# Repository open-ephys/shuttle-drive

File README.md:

# Shuttle-drive, the next gen. tetrode drive implant 

Tetrode arrays are the gold-standard method for neural recordings in many studies with behaving animals, especially for deep structures and chronic recordings. Here we outline an improved drive design for use in freely behaving animals. Our design makes use of recently developed technologies to reduce the complexity and build time of the drive while maintaining a low weight. The design also presents an improvement over many existing designs in terms of robustness and ease of use. We describe two variants: a 16 tetrode implant weighing ∼2 g for mice, bats, tree shrews and similar animals, and a 64 tetrode implant weighing ∼16 g for rats, and similar animals.These designs were co-developed and optimized alongside a new class of drive-mounted feature-rich amplifier boards with ultra-thin RF tethers, as described in an upcoming paper (Newman, Zhang et al., in prep). This design significantly improves the data yield of chronic electrophysiology experiments.

### Features

__64-Channel Drive__
- Channel count (small version): 18 drive mechanisms and up to 64 ephys channels per drive.
- Weight: ~2g for 16 tetrode drives.
- Build time:  < 1 day (small version).
- 4.5 mm travel distance, fully enclosed mechanism, low center of gravity. 

__256-Channel Drive__
- Channel count: 64 drive mechanisms and up to 256 ephys channels per drive.
- Weight: ~15g for 64 tetrode drives.
- 10 mm travel distance, fully enclosed mechanism, low center of gravity)

### Components & Availability

Ready-made drive components are available for purchase at the Open Ephy store
[here](http://www.open-ephys.org/drive-implant). All profits go towards
supporting the Open Ephys initiative if, and only if, parts are bought via this
store.

The drive consists of the following components:
- A 3d printed drive body
- 3d printed drive shuttles
- Polymicro (polyimide-coated quartz) shuttle tubes

These components can be purchased as bundle on our store:
- Polyimide tubes to make guide tube arrays 
- Custom screws (reusable) 
- Electrode interface boards (EIB) are available for 64 channel or 32 channel Omnetics headstages 

To assemble the drive and adjust tetrodes, an assembly jig and screwdriver are
needed. Both are available on the Open Ephys store.
- Assembly jig 
- Custom screwdriver 

### Building instructions & Documentation

For a quick initial overview, we provide a brief video detailing all the major steps of assembling the drive: [Assembly steps on youtube](https://www.youtube.com/watch?v=VBs4_pltE6o&feature=emb_logo).

The main documentation and building instructions are in the accompanying manuscript:

[Voigts et al.  An
easy-to-assemble, robust, and lightweight drive implant for chronic tetrode
recordings in freely moving animals](https://www.biorxiv.org/content/10.1101/746651v1). We recommend this manuscript as a starting point because it covers a lot of possible issues and goes into considerable detail on how to achieve the best results.

**A structured, up to date documentation is on the Open Ephys docs**: [https://open-ephys.github.io/shuttledrive-docs/](https://open-ephys.github.io/shuttledrive-docs/)

We also provide a [spreadsheet with step-by-step instructions](https://docs.google.com/spreadsheets/d/1qlOEyMCUptONbd9Ac4yKie1TxPHhV1puGx7GZTR9lvk/edit?usp=sharing), provided by Dimitra Vardalaki.

Finally, we encourage contributions from anyone, particularly additional information on variants and build instructions in nay form, including pull-requests or links to external documentation.

### Parts List / Bill of Materials
The bill of materials is located on this [google sheet](https://docs.google.com/spreadsheets/d/1LGhZMRnzcyo_r0Nunrh_lfmy5V0NHia-rGRHAYOWq4o/edit?usp=sharing)

### Citing this Work 
When using the Open Ephys shuttle drive implants, please cite the paper:

An easy-to-assemble, robust, and lightweight drive implant for chronic tetrode recordings in freely moving animals
J Voigts, JP Newman, MA Wilson, MT Harnett
Journal of Neural Engineering 17 (2), 026044
 [Link jne](https://iopscience.iop.org/article/10.1088/1741-2552/ab77f9/meta) [Link biorxiv](https://www.biorxiv.org/content/10.1101/746651v1) 

## License
Copyright Jakob Voigts, Jonathan P. Newman 2020.

<br />This work is licensed under a <a rel="license" href="http://creativecommons.org/licenses/by-nc-sa/3.0/igo/">Creative Commons Attribution-NonCommercial-ShareAlike 3.0 IGO License</a>.

If your are interested in obtaining a license to sell this device, please contact us at https://open-ephys.org/contact

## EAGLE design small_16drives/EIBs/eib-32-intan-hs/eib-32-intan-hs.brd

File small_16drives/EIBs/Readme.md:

# Omnetics EIBs for Open Ephys Shuttledrive

**(Deprecated)** We do not recommend using these EIBs any longer, instead consider switching to the hirose based EIBs (https://open-ephys.org/drive-implant/64-channel-eib-lyfw2) together with the newer low-profile headstage https://open-ephys.org/acquisition-system/low-profile-spi-headstage-64ch. In the longer term, consider using the upcoming ONIX system with this drive.

For the 64 channel variant, extra care is required to keep a precise alignment between the two omnetics connectors.

The EIB for the ONIX system and the SPI compatible low profile hedstage are found in the ONIX system repository at https://github.com/jonnew/ONIX/tree/main/eib-64

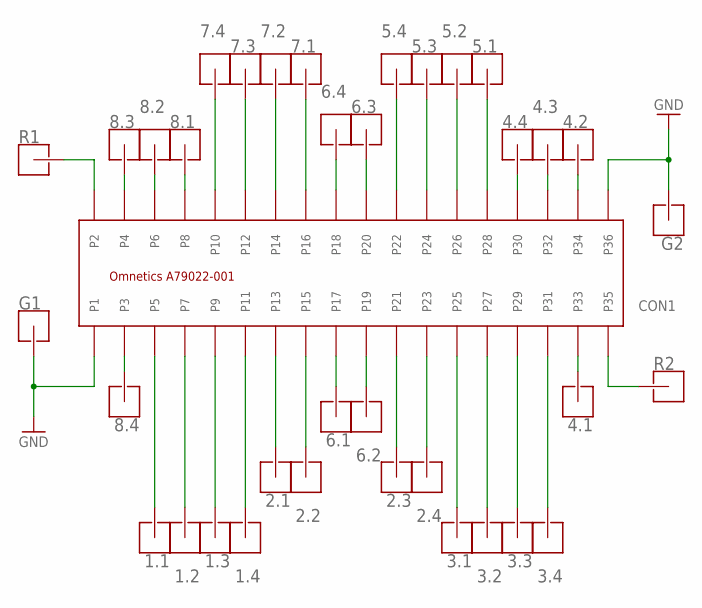
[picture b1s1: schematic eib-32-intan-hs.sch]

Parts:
1.1, 1.2, 1.3, 1.4, 2.1, 2.2, 2.3, 2.4, 3.1, 3.2, 3.3, 3.4, 4.1, 4.2, 4.3, 4.4, 5.1, 5.2, 5.3, 5.4, 6.1, 6.2, 6.3, 6.4, 7.1, 7.2, 7.3, 7.4, 8.1, 8.2, 8.3, 8.4: HOLE_L_G_PIN_V7; LARGE_GOLD_PIN_V7
CON1: A79022-001_MALESMD; A79026-001_MALE
G1, G2: HOLE_L_G_PIN_V7; LARGE_GOLD_PIN_V7
R1, R2: HOLE_L_G_PIN_V7; LARGE_GOLD_PIN_V7

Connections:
GND: CON1.P1, CON1.P36, G1.P$1, G2.P$1
unnamed: 1.1.P$1, CON1.P5
unnamed: 1.2.P$1, CON1.P7
unnamed: 1.3.P$1, CON1.P9
unnamed: 4.1.P$1, CON1.P33
unnamed: 4.3.P$1, CON1.P32
unnamed: 4.2.P$1, CON1.P34
unnamed: 1.4.P$1, CON1.P11
unnamed: 4.4.P$1, CON1.P30
unnamed: 6.1.P$1, CON1.P17
unnamed: 6.2.P$1, CON1.P19
unnamed: 6.3.P$1, CON1.P20
unnamed: 7.3.P$1, CON1.P12
unnamed: 2.1.P$1, CON1.P13
unnamed: 2.2.P$1, CON1.P15
unnamed: 2.3.P$1, CON1.P21
unnamed: 2.4.P$1, CON1.P23
unnamed: 3.1.P$1, CON1.P25
unnamed: 3.2.P$1, CON1.P27
unnamed: 3.3.P$1, CON1.P29
unnamed: 3.4.P$1, CON1.P31
unnamed: 6.4.P$1, CON1.P18
unnamed: 8.4.P$1, CON1.P3
unnamed: 8.3.P$1, CON1.P4
unnamed: 8.2.P$1, CON1.P6
unnamed: 8.1.P$1, CON1.P8
unnamed: 7.2.P$1, CON1.P14
unnamed: 7.1.P$1, CON1.P16
unnamed: 7.4.P$1, CON1.P10
unnamed: 5.1.P$1, CON1.P28
unnamed: 5.2.P$1, CON1.P26
unnamed: 5.4.P$1, CON1.P22
unnamed: 5.3.P$1, CON1.P24
unnamed: CON1.P2, R1.P$1
unnamed: CON1.P35, R2.P$1

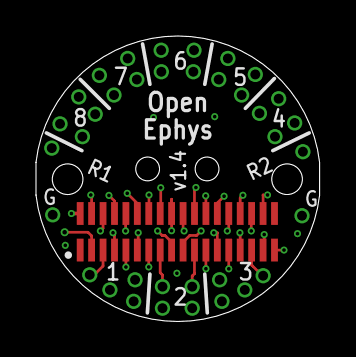
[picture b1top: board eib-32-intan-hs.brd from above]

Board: 4 copper layers, 15.8 x 15.9 mm, 37 parts (0 on the bottom side), 35 nets.

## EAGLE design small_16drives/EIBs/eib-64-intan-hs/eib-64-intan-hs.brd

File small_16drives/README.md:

# shuttleDrive-16

Mouse version of the next generation tetrode drive implant.

This is the variant for 16 drives.
The bill of materials can be found at https://docs.google.com/spreadsheets/d/1LGhZMRnzcyo_r0Nunrh_lfmy5V0NHia-rGRHAYOWq4o/edit?usp=sharing

Additional assembly instructions can be found at https://docs.google.com/spreadsheets/d/1qlOEyMCUptONbd9Ac4yKie1TxPHhV1puGx7GZTR9lvk/edit?usp=sharing

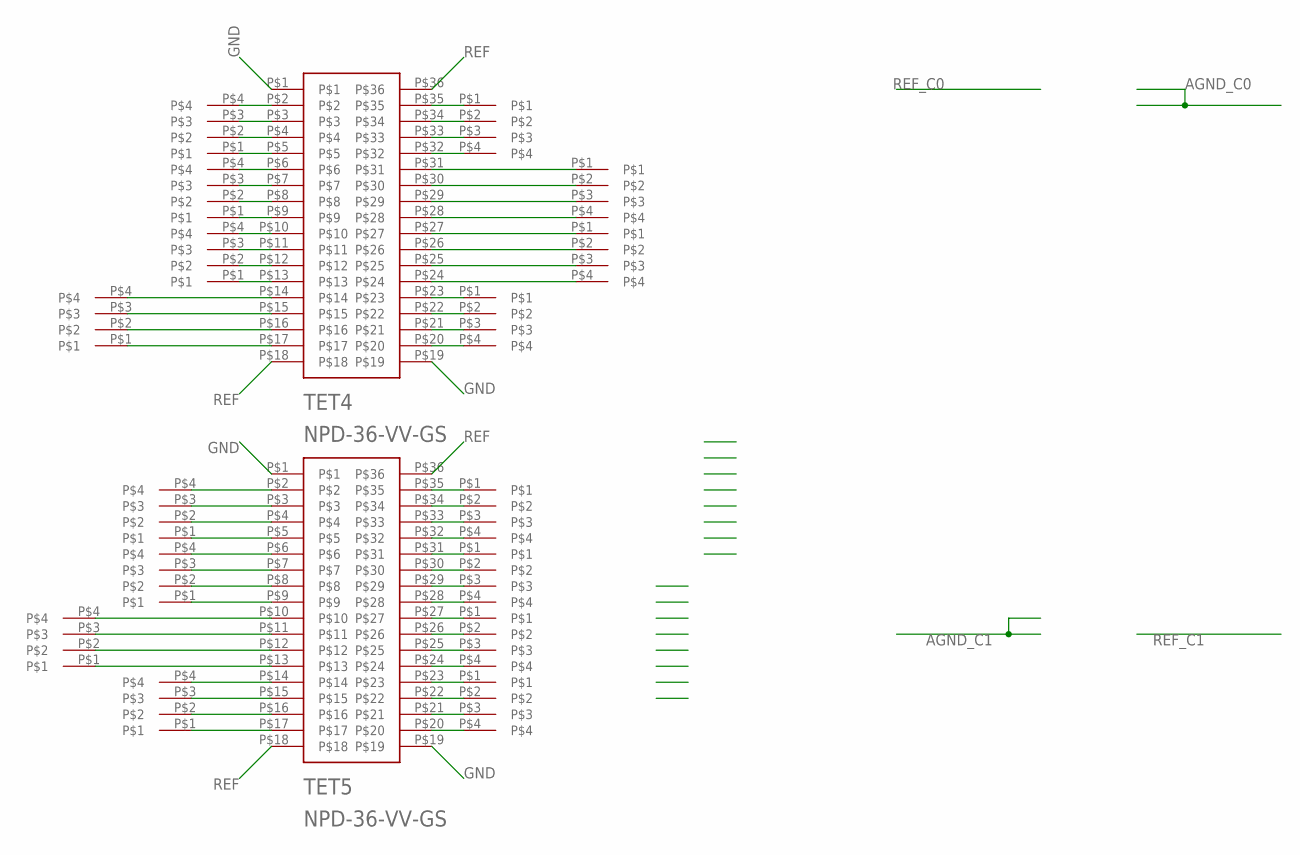
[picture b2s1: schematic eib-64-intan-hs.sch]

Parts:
TET0: 0; TET32
TET1: 1; TET32
TET2: 2; TET32
TET3: 3; TET32
TET4, TET5: NPD-36-VV-GS
TET8: 8; TET32
TET9: 9; TET32
TET10: 10; TET32
TET11: 11; TET32
TET12: 12; TET32
TET13: 13; TET32
TET14: 14; TET32
TET15: 15; TET32
TET20: 20; TET32
TET21: 21; TET32
TET22: 22; TET32
TET23: 23; TET32

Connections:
GND: TET4.P$1, TET4.P$19, TET5.P$1, TET5.P$19
unnamed: TET5.P$6, TET9.P$4
unnamed: TET5.P$2, TET8.P$4
unnamed: TET5.P$3, TET8.P$3
unnamed: TET5.P$4, TET8.P$2
unnamed: TET5.P$5, TET8.P$1
unnamed: TET5.P$7, TET9.P$3
unnamed: TET5.P$8, TET9.P$2
unnamed: TET5.P$9, TET9.P$1
unnamed: TET5.P$10, TET14.P$4
unnamed: TET5.P$11, TET14.P$3
unnamed: TET5.P$28, TET11.P$4
unnamed: TET5.P$27, TET12.P$1
unnamed: TET5.P$26, TET12.P$2
unnamed: TET5.P$25, TET12.P$3
unnamed: TET5.P$24, TET12.P$4
unnamed: TET5.P$23, TET13.P$1
unnamed: TET5.P$22, TET13.P$2
unnamed: TET5.P$21, TET13.P$3
unnamed: TET5.P$35, TET10.P$1
unnamed: TET5.P$34, TET10.P$2
unnamed: TET5.P$33, TET10.P$3
unnamed: TET5.P$32, TET10.P$4
unnamed: TET5.P$31, TET11.P$1
unnamed: TET5.P$30, TET11.P$2
unnamed: TET5.P$29, TET11.P$3
unnamed: TET5.P$12, TET14.P$2
unnamed: TET5.P$13, TET14.P$1
unnamed: TET5.P$14, TET15.P$4
unnamed: TET5.P$15, TET15.P$3
unnamed: TET5.P$16, TET15.P$2
unnamed: TET5.P$17, TET15.P$1
unnamed: TET1.P$4, TET4.P$2
unnamed: TET1.P$3, TET4.P$3
unnamed: TET1.P$2, TET4.P$4
unnamed: TET1.P$1, TET4.P$5
unnamed: TET0.P$4, TET4.P$6
unnamed: TET0.P$3, TET4.P$7
unnamed: TET0.P$2, TET4.P$8
unnamed: TET0.P$1, TET4.P$9
unnamed: TET3.P$1, TET4.P$35
unnamed: TET3.P$2, TET4.P$34
unnamed: TET3.P$3, TET4.P$33
unnamed: TET3.P$4, TET4.P$32
unnamed: TET2.P$1, TET4.P$31
unnamed: TET2.P$2, TET4.P$30
unnamed: TET5.P$20, TET13.P$4
unnamed: TET2.P$4, TET4.P$28
unnamed: TET4.P$27, TET21.P$1
unnamed: TET4.P$25, TET21.P$3
unnamed: TET4.P$26, TET21.P$2
unnamed: TET4.P$24, TET21.P$4
unnamed: TET4.P$23, TET20.P$1
unnamed: TET4.P$22, TET20.P$2
unnamed: TET4.P$21, TET20.P$3
unnamed: TET4.P$20, TET20.P$4
unnamed: TET4.P$10, TET23.P$4
unnamed: TET4.P$11, TET23.P$3
unnamed: TET4.P$12, TET23.P$2
unnamed: TET4.P$13, TET23.P$1
unnamed: TET4.P$14, TET22.P$4
unnamed: TET4.P$15, TET22.P$3
unnamed: TET4.P$16, TET22.P$2
unnamed: TET4.P$17, TET22.P$1
unnamed: TET2.P$3, TET4.P$29
REF: TET4.P$18, TET4.P$36, TET5.P$18, TET5.P$36

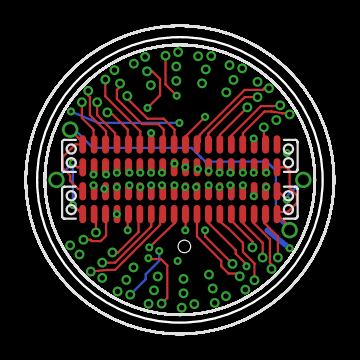
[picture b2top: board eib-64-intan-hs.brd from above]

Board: 4 copper layers, 15.9 x 15.9 mm, 18 parts (0 on the bottom side), 66 nets.

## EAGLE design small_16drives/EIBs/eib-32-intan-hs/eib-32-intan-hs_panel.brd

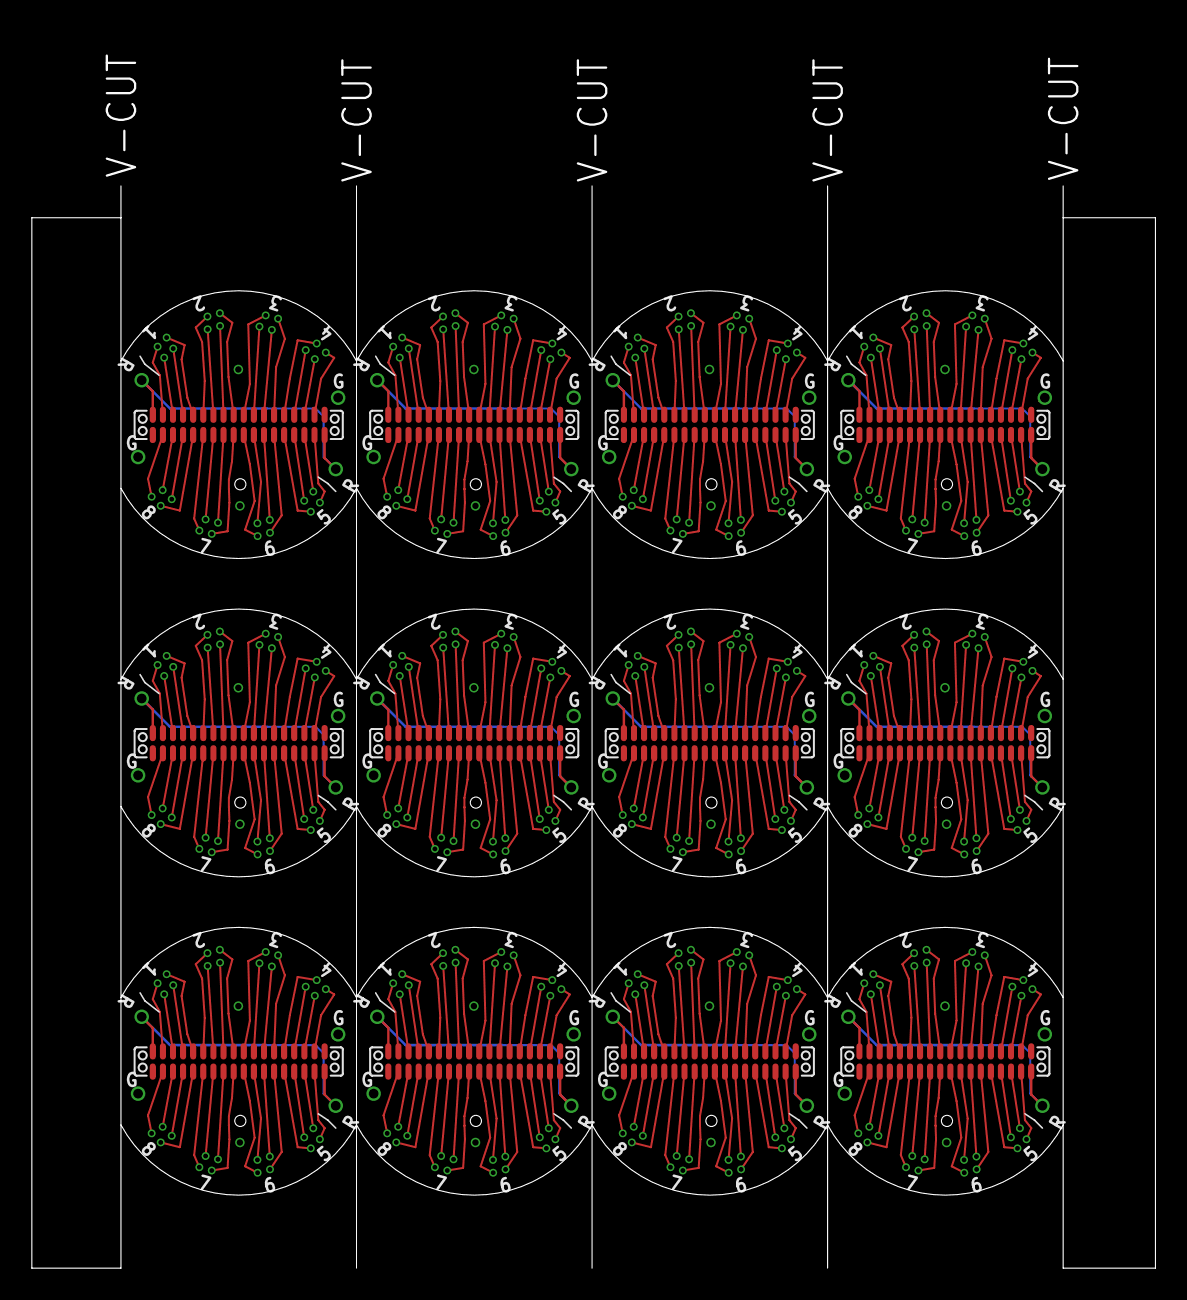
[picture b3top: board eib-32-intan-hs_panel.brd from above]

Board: 2 copper layers, 70.6 x 68.0 mm, 108 parts (0 on the bottom side), 397 nets.

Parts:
J1, J2, J3, J4, J5, J6, J7, J8, J9, J10, J11, J12: 4; NPD-36-VV-GS
TET1, TET9, TET17, TET25, TET33, TET41, TET49, TET57, TET64, TET73, TET81, TET89: 0; TET8
TET2, TET10, TET18, TET26, TET34, TET42, TET50, TET58, TET65, TET74, TET82, TET90: 1; TET8
TET3, TET11, TET19, TET27, TET35, TET43, TET51, TET59, TET66, TET75, TET83, TET91: 4; TET8
TET4, TET12, TET20, TET28, TET36, TET44, TET52, TET60, TET67, TET76, TET84, TET92: 5; TET8
TET5, TET13, TET21, TET29, TET37, TET45, TET53, TET61, TET68, TET77, TET85, TET93: 6; TET8
TET6, TET14, TET22, TET30, TET38, TET46, TET54, TET62, TET69, TET78, TET86, TET94: 7; TET8
TET7, TET15, TET23, TET31, TET39, TET47, TET55, TET63, TET70, TET79, TET87, TET95: 10; TET8
TET8, TET16, TET24, TET32, TET40, TET48, TET56, TET71, TET72, TET80, TET88, TET96: 11; TET8

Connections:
GND: J1.P$1, J1.P$19, J2.P$1, J2.P$19, J3.P$1, J3.P$19, J4.P$1, J4.P$19, J5.P$1, J5.P$19, J6.P$1, J6.P$19, J7.P$1, J7.P$19, J8.P$1, J8.P$19, J9.P$1, J9.P$19, J10.P$1, J10.P$19, J11.P$1, J11.P$19, J12.P$1, J12.P$19
unnamed: J1.P$35, TET2.P$1
unnamed: J1.P$32, TET2.P$2
unnamed: J1.P$33, TET2.P$3
unnamed: J1.P$34, TET2.P$4
unnamed: J1.P$28, TET1.P$2
unnamed: J1.P$30, TET1.P$4
unnamed: J1.P$29, TET1.P$3
unnamed: J1.P$31, TET1.P$1
unnamed: J1.P$27, TET8.P$1
unnamed: J1.P$24, TET8.P$2
unnamed: J1.P$26, TET8.P$4
unnamed: J1.P$25, TET8.P$3
unnamed: J1.P$23, TET7.P$1
unnamed: J1.P$20, TET7.P$2
unnamed: J1.P$22, TET7.P$4
unnamed: J1.P$21, TET7.P$3
unnamed: J1.P$17, TET6.P$1
unnamed: J1.P$14, TET6.P$2
unnamed: J1.P$16, TET6.P$4
unnamed: J1.P$15, TET6.P$3
unnamed: J1.P$13, TET5.P$1
unnamed: J1.P$9, TET4.P$1
unnamed: J1.P$5, TET3.P$1
unnamed: J1.P$10, TET5.P$2
unnamed: J1.P$12, TET5.P$4
unnamed: J1.P$11, TET5.P$3
unnamed: J1.P$7, TET4.P$3
unnamed: J1.P$8, TET4.P$4
unnamed: J1.P$6, TET4.P$2
unnamed: J1.P$3, TET3.P$3
unnamed: J1.P$4, TET3.P$4
unnamed: J1.P$2, TET3.P$2
unnamed: J2.P$35, TET10.P$1
unnamed: J2.P$32, TET10.P$2
unnamed: J2.P$33, TET10.P$3
unnamed: J2.P$34, TET10.P$4
unnamed: J2.P$28, TET9.P$2
unnamed: J2.P$30, TET9.P$4
unnamed: J2.P$29, TET9.P$3
unnamed: J2.P$31, TET9.P$1
unnamed: J2.P$27, TET16.P$1
unnamed: J2.P$24, TET16.P$2
unnamed: J2.P$26, TET16.P$4
unnamed: J2.P$25, TET16.P$3
unnamed: J2.P$23, TET15.P$1
unnamed: J2.P$20, TET15.P$2
unnamed: J2.P$22, TET15.P$4
unnamed: J2.P$21, TET15.P$3
unnamed: J2.P$17, TET14.P$1
unnamed: J2.P$14, TET14.P$2
unnamed: J2.P$16, TET14.P$4
unnamed: J2.P$15, TET14.P$3
unnamed: J2.P$13, TET13.P$1
unnamed: J2.P$9, TET12.P$1
unnamed: J2.P$5, TET11.P$1
unnamed: J2.P$10, TET13.P$2
unnamed: J2.P$12, TET13.P$4
unnamed: J2.P$11, TET13.P$3
unnamed: J2.P$7, TET12.P$3
unnamed: J2.P$8, TET12.P$4
unnamed: J2.P$6, TET12.P$2
unnamed: J2.P$3, TET11.P$3
unnamed: J2.P$4, TET11.P$4
unnamed: J2.P$2, TET11.P$2
unnamed: J3.P$35, TET18.P$1
unnamed: J3.P$32, TET18.P$2
unnamed: J3.P$33, TET18.P$3
unnamed: J3.P$34, TET18.P$4
unnamed: J3.P$28, TET17.P$2
unnamed: J3.P$30, TET17.P$4
unnamed: J3.P$29, TET17.P$3
unnamed: J3.P$31, TET17.P$1
unnamed: J3.P$27, TET24.P$1
unnamed: J3.P$24, TET24.P$2
unnamed: J3.P$26, TET24.P$4
unnamed: J3.P$25, TET24.P$3
unnamed: J3.P$23, TET23.P$1
unnamed: J3.P$20, TET23.P$2
unnamed: J3.P$22, TET23.P$4
unnamed: J3.P$21, TET23.P$3
unnamed: J3.P$17, TET22.P$1
unnamed: J3.P$14, TET22.P$2
unnamed: J3.P$16, TET22.P$4
unnamed: J3.P$15, TET22.P$3
unnamed: J3.P$13, TET21.P$1
unnamed: J3.P$9, TET20.P$1
unnamed: J3.P$5, TET19.P$1
unnamed: J3.P$10, TET21.P$2
unnamed: J3.P$12, TET21.P$4
unnamed: J3.P$11, TET21.P$3
unnamed: J3.P$7, TET20.P$3
unnamed: J3.P$8, TET20.P$4
unnamed: J3.P$6, TET20.P$2
unnamed: J3.P$3, TET19.P$3
unnamed: J3.P$4, TET19.P$4
unnamed: J3.P$2, TET19.P$2
unnamed: J4.P$35, TET26.P$1
unnamed: J4.P$32, TET26.P$2
unnamed: J4.P$33, TET26.P$3
unnamed: J4.P$34, TET26.P$4
unnamed: J4.P$28, TET25.P$2
unnamed: J4.P$30, TET25.P$4
unnamed: J4.P$29, TET25.P$3
unnamed: J4.P$31, TET25.P$1
unnamed: J4.P$27, TET32.P$1
unnamed: J4.P$24, TET32.P$2
unnamed: J4.P$26, TET32.P$4
unnamed: J4.P$25, TET32.P$3
unnamed: J4.P$23, TET31.P$1
unnamed: J4.P$20, TET31.P$2
unnamed: J4.P$22, TET31.P$4
unnamed: J4.P$21, TET31.P$3
unnamed: J4.P$17, TET30.P$1
unnamed: J4.P$14, TET30.P$2
unnamed: J4.P$16, TET30.P$4
unnamed: J4.P$15, TET30.P$3
unnamed: J4.P$13, TET29.P$1
unnamed: J4.P$9, TET28.P$1
unnamed: J4.P$5, TET27.P$1
unnamed: J4.P$10, TET29.P$2
unnamed: J4.P$12, TET29.P$4
unnamed: J4.P$11, TET29.P$3
unnamed: J4.P$7, TET28.P$3
unnamed: J4.P$8, TET28.P$4
unnamed: J4.P$6, TET28.P$2
unnamed: J4.P$3, TET27.P$3
unnamed: J4.P$4, TET27.P$4
unnamed: J4.P$2, TET27.P$2
unnamed: J6.P$35, TET34.P$1
unnamed: J6.P$32, TET34.P$2
unnamed: J6.P$33, TET34.P$3
unnamed: J6.P$34, TET34.P$4
unnamed: J6.P$28, TET33.P$2
unnamed: J6.P$30, TET33.P$4
unnamed: J6.P$29, TET33.P$3
unnamed: J6.P$31, TET33.P$1
unnamed: J6.P$27, TET40.P$1
unnamed: J6.P$24, TET40.P$2
unnamed: J6.P$26, TET40.P$4
unnamed: J6.P$25, TET40.P$3
unnamed: J6.P$23, TET39.P$1
unnamed: J6.P$20, TET39.P$2
unnamed: J6.P$22, TET39.P$4
unnamed: J6.P$21, TET39.P$3
unnamed: J6.P$17, TET38.P$1
unnamed: J6.P$14, TET38.P$2
unnamed: J6.P$16, TET38.P$4
unnamed: J6.P$15, TET38.P$3
unnamed: J6.P$13, TET37.P$1
unnamed: J6.P$9, TET36.P$1
unnamed: J6.P$5, TET35.P$1
unnamed: J6.P$10, TET37.P$2
unnamed: J6.P$12, TET37.P$4
unnamed: J6.P$11, TET37.P$3
unnamed: J6.P$7, TET36.P$3
unnamed: J6.P$8, TET36.P$4
unnamed: J6.P$6, TET36.P$2
unnamed: J6.P$3, TET35.P$3
unnamed: J6.P$4, TET35.P$4
unnamed: J6.P$2, TET35.P$2
unnamed: J7.P$35, TET42.P$1
unnamed: J7.P$32, TET42.P$2
unnamed: J7.P$33, TET42.P$3
unnamed: J7.P$34, TET42.P$4
unnamed: J7.P$28, TET41.P$2
unnamed: J7.P$30, TET41.P$4
unnamed: J7.P$29, TET41.P$3
unnamed: J7.P$31, TET41.P$1
unnamed: J7.P$27, TET48.P$1
unnamed: J7.P$24, TET48.P$2
unnamed: J7.P$26, TET48.P$4
unnamed: J7.P$25, TET48.P$3
unnamed: J7.P$23, TET47.P$1
unnamed: J7.P$20, TET47.P$2
unnamed: J7.P$22, TET47.P$4
unnamed: J7.P$21, TET47.P$3
unnamed: J7.P$17, TET46.P$1
unnamed: J7.P$14, TET46.P$2
unnamed: J7.P$16, TET46.P$4
unnamed: J7.P$15, TET46.P$3
unnamed: J7.P$13, TET45.P$1
unnamed: J7.P$9, TET44.P$1
unnamed: J7.P$5, TET43.P$1
unnamed: J7.P$10, TET45.P$2
unnamed: J7.P$12, TET45.P$4
unnamed: J7.P$11, TET45.P$3
unnamed: J7.P$7, TET44.P$3
unnamed: J7.P$8, TET44.P$4
unnamed: J7.P$6, TET44.P$2
unnamed: J7.P$3, TET43.P$3
unnamed: J7.P$4, TET43.P$4
unnamed: J7.P$2, TET43.P$2
unnamed: J8.P$35, TET50.P$1
unnamed: J8.P$32, TET50.P$2
unnamed: J8.P$33, TET50.P$3
unnamed: J8.P$34, TET50.P$4
unnamed: J8.P$28, TET49.P$2
unnamed: J8.P$30, TET49.P$4
unnamed: J8.P$29, TET49.P$3
unnamed: J8.P$31, TET49.P$1
unnamed: J8.P$27, TET56.P$1
unnamed: J8.P$24, TET56.P$2
unnamed: J8.P$26, TET56.P$4
unnamed: J8.P$25, TET56.P$3
unnamed: J8.P$23, TET55.P$1
unnamed: J8.P$20, TET55.P$2
unnamed: J8.P$22, TET55.P$4
unnamed: J8.P$21, TET55.P$3
unnamed: J8.P$17, TET54.P$1
unnamed: J8.P$14, TET54.P$2
unnamed: J8.P$16, TET54.P$4
unnamed: J8.P$15, TET54.P$3
unnamed: J8.P$13, TET53.P$1
unnamed: J8.P$9, TET52.P$1
unnamed: J8.P$5, TET51.P$1
unnamed: J8.P$10, TET53.P$2
unnamed: J8.P$12, TET53.P$4
unnamed: J8.P$11, TET53.P$3
unnamed: J8.P$7, TET52.P$3
unnamed: J8.P$8, TET52.P$4
unnamed: J8.P$6, TET52.P$2
unnamed: J8.P$3, TET51.P$3
unnamed: J8.P$4, TET51.P$4
unnamed: J8.P$2, TET51.P$2
unnamed: J9.P$35, TET58.P$1
unnamed: J9.P$32, TET58.P$2
unnamed: J9.P$33, TET58.P$3
unnamed: J9.P$34, TET58.P$4
unnamed: J9.P$28, TET57.P$2
unnamed: J9.P$30, TET57.P$4
unnamed: J9.P$29, TET57.P$3
unnamed: J9.P$31, TET57.P$1
unnamed: J9.P$27, TET72.P$1
unnamed: J9.P$24, TET72.P$2
unnamed: J9.P$26, TET72.P$4
unnamed: J9.P$25, TET72.P$3
unnamed: J9.P$23, TET63.P$1
unnamed: J9.P$20, TET63.P$2
unnamed: J9.P$22, TET63.P$4
unnamed: J9.P$21, TET63.P$3
unnamed: J9.P$17, TET62.P$1
unnamed: J9.P$14, TET62.P$2
unnamed: J9.P$16, TET62.P$4
unnamed: J9.P$15, TET62.P$3
unnamed: J9.P$13, TET61.P$1
unnamed: J9.P$9, TET60.P$1
unnamed: J9.P$5, TET59.P$1
unnamed: J9.P$10, TET61.P$2
unnamed: J9.P$12, TET61.P$4
unnamed: J9.P$11, TET61.P$3
unnamed: J9.P$7, TET60.P$3
unnamed: J9.P$8, TET60.P$4
unnamed: J9.P$6, TET60.P$2
unnamed: J9.P$3, TET59.P$3
unnamed: J9.P$4, TET59.P$4
unnamed: J9.P$2, TET59.P$2
unnamed: J5.P$35, TET65.P$1
unnamed: J5.P$32, TET65.P$2
unnamed: J5.P$33, TET65.P$3
unnamed: J5.P$34, TET65.P$4
unnamed: J5.P$28, TET64.P$2
unnamed: J5.P$30, TET64.P$4
unnamed: J5.P$29, TET64.P$3
unnamed: J5.P$31, TET64.P$1
unnamed: J5.P$27, TET71.P$1
unnamed: J5.P$24, TET71.P$2
unnamed: J5.P$26, TET71.P$4
unnamed: J5.P$25, TET71.P$3
unnamed: J5.P$23, TET70.P$1
unnamed: J5.P$20, TET70.P$2
unnamed: J5.P$22, TET70.P$4
unnamed: J5.P$21, TET70.P$3
unnamed: J5.P$17, TET69.P$1
unnamed: J5.P$14, TET69.P$2
unnamed: J5.P$16, TET69.P$4
unnamed: J5.P$15, TET69.P$3
unnamed: J5.P$13, TET68.P$1
unnamed: J5.P$9, TET67.P$1
unnamed: J5.P$5, TET66.P$1
unnamed: J5.P$10, TET68.P$2
unnamed: J5.P$12, TET68.P$4
unnamed: J5.P$11, TET68.P$3
unnamed: J5.P$7, TET67.P$3
unnamed: J5.P$8, TET67.P$4
unnamed: J5.P$6, TET67.P$2
unnamed: J5.P$3, TET66.P$3
unnamed: J5.P$4, TET66.P$4
unnamed: J5.P$2, TET66.P$2
unnamed: J10.P$35, TET74.P$1
unnamed: J10.P$32, TET74.P$2
unnamed: J10.P$33, TET74.P$3
unnamed: J10.P$34, TET74.P$4
unnamed: J10.P$28, TET73.P$2
unnamed: J10.P$30, TET73.P$4
unnamed: J10.P$29, TET73.P$3
unnamed: J10.P$31, TET73.P$1
unnamed: J10.P$27, TET80.P$1
unnamed: J10.P$24, TET80.P$2
unnamed: J10.P$26, TET80.P$4
unnamed: J10.P$25, TET80.P$3
unnamed: J10.P$23, TET79.P$1
unnamed: J10.P$20, TET79.P$2
unnamed: J10.P$22, TET79.P$4
unnamed: J10.P$21, TET79.P$3
unnamed: J10.P$17, TET78.P$1
unnamed: J10.P$14, TET78.P$2
unnamed: J10.P$16, TET78.P$4
unnamed: J10.P$15, TET78.P$3
unnamed: J10.P$13, TET77.P$1
unnamed: J10.P$9, TET76.P$1
unnamed: J10.P$5, TET75.P$1
unnamed: J10.P$10, TET77.P$2
unnamed: J10.P$12, TET77.P$4
unnamed: J10.P$11, TET77.P$3
unnamed: J10.P$7, TET76.P$3
unnamed: J10.P$8, TET76.P$4
unnamed: J10.P$6, TET76.P$2
unnamed: J10.P$3, TET75.P$3
unnamed: J10.P$4, TET75.P$4
unnamed: J10.P$2, TET75.P$2
unnamed: J11.P$35, TET82.P$1
unnamed: J11.P$32, TET82.P$2
unnamed: J11.P$33, TET82.P$3
unnamed: J11.P$34, TET82.P$4
unnamed: J11.P$28, TET81.P$2
unnamed: J11.P$30, TET81.P$4
unnamed: J11.P$29, TET81.P$3
unnamed: J11.P$31, TET81.P$1
unnamed: J11.P$27, TET88.P$1
unnamed: J11.P$24, TET88.P$2
unnamed: J11.P$26, TET88.P$4
unnamed: J11.P$25, TET88.P$3
unnamed: J11.P$23, TET87.P$1
unnamed: J11.P$20, TET87.P$2
unnamed: J11.P$22, TET87.P$4
unnamed: J11.P$21, TET87.P$3
unnamed: J11.P$17, TET86.P$1
unnamed: J11.P$14, TET86.P$2
unnamed: J11.P$16, TET86.P$4
unnamed: J11.P$15, TET86.P$3
unnamed: J11.P$13, TET85.P$1
unnamed: J11.P$9, TET84.P$1
unnamed: J11.P$5, TET83.P$1
unnamed: J11.P$10, TET85.P$2
unnamed: J11.P$12, TET85.P$4
unnamed: J11.P$11, TET85.P$3
unnamed: J11.P$7, TET84.P$3
unnamed: J11.P$8, TET84.P$4
unnamed: J11.P$6, TET84.P$2
unnamed: J11.P$3, TET83.P$3
unnamed: J11.P$4, TET83.P$4
unnamed: J11.P$2, TET83.P$2
unnamed: J12.P$35, TET90.P$1
unnamed: J12.P$32, TET90.P$2
unnamed: J12.P$33, TET90.P$3
unnamed: J12.P$34, TET90.P$4
unnamed: J12.P$28, TET89.P$2
unnamed: J12.P$30, TET89.P$4
unnamed: J12.P$29, TET89.P$3
unnamed: J12.P$31, TET89.P$1
unnamed: J12.P$27, TET96.P$1
unnamed: J12.P$24, TET96.P$2
unnamed: J12.P$26, TET96.P$4
unnamed: J12.P$25, TET96.P$3
unnamed: J12.P$23, TET95.P$1
unnamed: J12.P$20, TET95.P$2
unnamed: J12.P$22, TET95.P$4
unnamed: J12.P$21, TET95.P$3
unnamed: J12.P$17, TET94.P$1
unnamed: J12.P$14, TET94.P$2
unnamed: J12.P$16, TET94.P$4
unnamed: J12.P$15, TET94.P$3
unnamed: J12.P$13, TET93.P$1
unnamed: J12.P$9, TET92.P$1
unnamed: J12.P$5, TET91.P$1
unnamed: J12.P$10, TET93.P$2
unnamed: J12.P$12, TET93.P$4
unnamed: J12.P$11, TET93.P$3
unnamed: J12.P$7, TET92.P$3
unnamed: J12.P$8, TET92.P$4
unnamed: J12.P$6, TET92.P$2
unnamed: J12.P$3, TET91.P$3
unnamed: J12.P$4, TET91.P$4
unnamed: J12.P$2, TET91.P$2
REF1: J1.P$18, J1.P$36
REF2: J2.P$18, J2.P$36
REF3: J3.P$18, J3.P$36
REF4: J5.P$18, J5.P$36
REF5: J4.P$18, J4.P$36
REF6: J6.P$18, J6.P$36
REF7: J7.P$18, J7.P$36
REF8: J8.P$18, J8.P$36
REF9: J9.P$18, J9.P$36
REF10: J10.P$18, J10.P$36
REF11: J11.P$18, J11.P$36
REF12: J12.P$18, J12.P$36

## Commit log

2019-07-22 Updated readme with abstract
2019-07-22 added image ref to readme
2019-07-22 added img
2019-07-22 fixed image link in readme
2019-08-23 updated readme
    added more info and link to BOM
2019-08-24 initial commit mouse drive
2019-08-25 added biorxiv link
2019-09-10 Update README.md
    - Fix broken links and text formatting
2019-09-19 Cleanup repo metadata
    - Numerous fixes to README. Typos, etc.
    - Add proper license materials to repo
2019-09-19 Added large drive design files to repo
2019-09-19 Update README for large drive
2019-09-19 Update README.md
    - Add link to interest survey on OE website
2019-11-07 added screw designs
2019-11-18 added rat drive jig
2020-02-20 Add files via upload
    I redesigned the rat shuttle. The hooks are now longer, and the shuttles have a cutout so that they can be easily grabbed with forceps.
2020-02-20 Delete rat_drive_shuttle_short_palletized.SLDPRT
    We shouldn't need this since it's part of the palletized version.
2020-02-20 Add files via upload
    I accidentally deleted this file (palletized version) instead of the single shuttle file.
2020-02-20 Delete rat_drive_shuttle_short.SLDPRT
    We shouldn't need this because a single shuttle can be found in the palletized version / file.
2020-07-01 added bilaterral variant
2020-07-26 Changed license to Creative Commons by-nc-sa
2020-12-02 Added old omnetics EIB designs
2020-12-02 Added link to ONIX eib64
2021-01-29 Updated EIB holders for jig
    now has 2 options for large and small offsets
2022-04-15 Update README.md
    added link to docs

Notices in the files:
small_16drives/EIBs/eib-64-intan-hs/eib-64-intan-hs.sch:
LICENSE: CERN OHL v1.2
